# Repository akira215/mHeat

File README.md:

# mHeat
Monitoring HomeBus device and Modbus, embedded sofware on dedicated PCB using ESP32C6 µC

# Description

This repository contain all the development for an electronic device that will monitor a water tank (such as rain collect tank) using zigbee to transmit data to a coordinator. It contains: 
 * A PCB design [PCB design](PCB/README.md)
 * An enclosure design to be printed in 3D [Enclosure design](3Dprint/README.md)
 * Source code of the embedded software on the board (in an ESP32C6 µC)
 * An External converter for Zigbee2MQTT service [external converter](external_converters)

# Principle

The board will collect data from various sensors surch as:
 * Upstream static pressure (pump side)
 * Downstream static pressure (home side) - difference between upstream and downstream static pressure is used to estimate filters clogging
 * Water level sensor, to estimate the available water volume in the tank
 * water pulse meter to count the consumption in the home
 * Additionally on board temperature sensor could be monitor

 The 3 first sensors shall be 4-20mA sensor directly connected to the board. The water counter shall be a dry contact meter, connected to the board

 All these sensors have a calibration factor that can be updated directly form Zigbee2MQTT GUI. To avoid losing calibration, the device itself will keep updated theses factor in its Non Volatile Storage.

A 4-20mA input is available for any other futher sensor requirement. Adding a sensor will require to :
 * Update the embedded software
 * Update the external converter on Zigbee2MQTT side

## Usage

  * Short press button to join the zigbee network (coordinator shall grant pairing) -> LED shall flash, until network is joined, it then shutoff
  * Long press button to leave network. When the LED is fixed on, the device is not connected to the network neither is trying to join

## Sensor selection

### Upstream and downstream static pressure

  Regular pressure transmitter are not so expensive and efficient for that purpose. These 2 sensors shall have a measured range according to installation pressure. In regular network, pressure is limited to 3 bars, so selecting a sensor 0-5 bars seems a good choice. If the upper value is higher, the resolution of the measurement will be less as the ADC converter resolution is fixed.

  The shunt to convert current to tension for the ADC converter is 133R, and Imax for the sensor @max range will be 20mA so Umax for ADS1115 will be 2.66V (U=R*I). 5 bars = 500 kPa, so the calibration factor shall be 500 kPa / 2.66V = 187.97 kPa/V. Of course this factor shall be adjusted by measuring at the same location of one sensor the pressure, and correcting the reading of the sensor, but this short computation can help to start setting up calibration factor

### Water level

  Whatever technology of sensor could be used as soon as its output is 4-20mA current. Tests have been done using submerged differential pressure sensor, with the balance pipe to get the atmospheric pressure that run with the electrical cable, they worked properly. The range of this sensor shall be in accordance with the depth of the tank. The output value of Zigbee2MQTT will be a % of depth (meaning 100% when tank is full). Depending on the shape and cross section of the tank, this could be converted to a volume directly in the Z2M external converter, or outside Z2M in another software.

  The shunt to convert current to tension for the ADC converter is 133R, and Imax for the sensor @max range will be 20mA so Umax for ADS1115 will be 2.66V (U=R*I). For 100% the calibration factor shall be 100% / 2.66V = 37.594 %/V. 
  
  Of course this factor shall be adjusted when tank is full to read 100% in the Zigbee2MQTT output. For example, if yo have a 0-2m sensor and the require stroke of your tank (max height - min height before depriming pump) is 1.5m, it means that the 100% value of your tank will occur when sensor will read 1.5m (take care to install the sensor just before depriming pump). The voltage at the converter will be 1.5m/2m * 2.66V = 1.995V, so you will have to set the calibration factor considering 100% / 1.995V = 50.125%/V

### Water pulse counter

  The water meter shall send a pulse each XX L, whatever XX is. It is expected to have a dry contact that switch on and off each pulse. Hardware debouncer has been implemented for a particular counter, measuring bouncing using an oscilloscope. Computation of this RC filter has been provided here:
  [Spreadsheet](<PCB/2024-06-29 Comput.ods>)
    
  The kFactor to be set up in Zigbee2MQTT is only the L per pulse of the counter.

## Zigbee2MQTT integration

### External converter

External converter shall be loaded according to Zigbee2MQTT instructions:

[Zigbee2MQTT external converters](https://www.zigbee2mqtt.io/advanced/more/external_converters.html)

Restart Zigbee2MQTT `Webpage > Settings > Tools > Restart Zigbee2MQTT`

### Pairing zTank device

If the LED is fixed on, short press one time on the button, this will put the device in pairing mode.
Device is in Pairing Mode when the LED flahes quickly. 

Put Coordinator (or other device) in pairing mode using Zigbee2MQTT GUI (antenna symbol on the upper right of the screen with mention `All`)

After a short time, LED shall stop flashing. When LED is off, device is paired. You can check on Zigbee2MQTT device list

### Device icon

To add an icon in Zigbee2MQTT GUI, create a folder named `device_icon` in the root of Zigbee2MQTT docker installation (folder containing `configuration.yml`). In that foler, put the `zTank_icon.png` file contained in the `img` directory of this repository.

On Zigbee2MQTT GUI, go to `Devices` list and click on the device. Go to `Settings` tab and scroll down to the `icon` box.
Put `device_icons/zTank_icon.png` in that box. Icon shall be visible on Zigbee2MQTT GUI.

### Reporting

To develop*******************************************************************

## Build Instructions

The embedded software required `esp-ash-components`:

```
git submodule add https://github.com/akira215/esp-ash-components.git components
```

Create a partition.csv for zigbee and configure menuconfig with custom partition table (shall be done by default)

## Configuration

Configuration is available in `menuconfig` in the `Project setting` section:

### Pin Layout

  This section refer to hardware connection of LED button and volume meter. <span style="color:red">**These settings shall not be changed unless new hardware is developped.**</span>

### Zigbee endpoints

  This section refer to the endpoint for each sensor of the device. Any change in this number require to update the external converter accordingly

  And in Zigbee2MQTT external converter:

### Zigbee device

  Zigbee stack has been sized doing extensive tests. <span style="color:red">**This setting shall not be changed.**</span>

### ADS Pin Layout

  This section refer to hardware connection of ADS1115 converter to µC pin. <span style="color:red">**These settings shall not be changed unless new hardware is developped.**</span>

### ADS Converter config

  The first 3 inputs refer to the channel in which each sensor is connected. Take care that channel are not implemented on the connector in a logical order, so please refer to pictures that describe which pins of the connector is connected to which ADC channel (and polarity for sensors)

  The delay between 2 queries of ADS is the update rate of the measurement. Between 2 measurement, ADS is put in sleep to optimize consumption. Take care that driver will trigger one conversion for each channel, so there is a minimal time between 2 queries, depending on the resolution set for the ADS.

  The delay between 2 queries of temperature is the update rate of the measurement of the internal µC temperature sensor.

## Current Status

Still work in progress, but is completely running. All bugs 
could be reported to try to improve it.

## PCB design

[PCB design](PCB/README.md)

## Enclosure design design

[Enclosure design](3Dprint/README.md)

## Caveats

### To be developped

OTA update

## Usage and Examples

## Changes

### New in version 0.0.0

## Credits

 * [Zigbee2MQTT](https://github.com/Koenkk/zigbee2mqtt)

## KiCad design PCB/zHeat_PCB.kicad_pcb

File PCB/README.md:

# zHeat PCB
A dedicated PCB using ESP32C6 µC as been designed to optimize reliability and costs.

The board connect to:

* Homebus to connect Daikin Heat Pump via P1P2 connector

* 12V serial bus to connect on heating circuit controller

* 4-20mA port to connect to pressure sensor on the circuit

## Tools

 The design of the PCB has been done with KiCad 10.0. Particular footprint and 3D STEP file are included in the `/library` folder for sake of maintenance

## Design

 The design is based on ESP32C6 WROOM with the following peripherials:
 * USB for power, flash device and output serial debug / info.
 * Powering circuit is done using MCP1826S 
 * A 4-20mA loop is built based on a LM2735X (1.6MHz) to raise voltage to about 20V
 * 4 channels 4-20mA sensors is provided and converted using ADS1115IDGS. It communicate with µC with i2c port
 * a debounced contact is provided for pulse counter
 * A push button is also provided for very simple HMI
 * PCB is also equipped by a LED for simpl HMI
 * Finally PCB is equipped with header that can be used for a touchscreen device in case of future needs (software lib already written and tested)

 Component size has been selected to 0805, except ESD protective diodes that are smaller.

### USB

  USB socket is grounded to the main ground planes (2 sides).
  USB Lines `USB-` and `USB+` are directly connected to ESP32C6 to flash and monitor µC.
  `VBUS` is used to provide `+5V` (which is in fact lower than +5V) via a protective diode `D3`.

  All this 3 lines are protected by ESD protective diode.

### Voltage regulator

  All the board is powered using `+3.3V`. This voltage is provided by a fixed low-voltage regulator MCP1826S-3302E that can provide up to 1000mA.
  Fixed voltage regulator requires only few external component, in this case only capacitors are installed as per datasheet.

### 4-20mA Voltage circuit

  To avoid noise on lines and due to voltage drop at each stage, 4-20mA loop voltage shall be at around 20V. Care shall be taken when changing this voltage as it may require adjustment (in the shunt values for instance) to avoid damaging other components.

  This voltage is produced from `+5V` using a boost type regulator LM2735X (@1.6MHz). Computation of the external components are provided in the LibreOffice Spreadsheet [PCB comput spreadsheet](<2024-06-29 Comput.ods>). A 33µH inductance has been selected to get a clean output voltage to avoid noise on sensors line.

### 4-20mA conversion

  4 channels are available via Phoenix contact 8 poles connector. Each channel input current is injected in a 133R shunt (low tolerance resistor) to output a voltage below 3.3V. A 100nF capacitor is provided to reduce noise.

  Each channel voltage is then converted in a digital signal using an ADS1115IDGS, that communicate with µC using i2c protocol. A ready pin is used to trigger an interrupt to the µC when data are available.
  External components are:
   * 10k resistor connected to the ground for the address of the device (only one on board so gnd is the common one)
   * 10k pull-up resistor on each signal (`SCL`, `SDA`, `RDY`) connected to µC
   * Decoupling capacitor for power lines and rearmable fuse to protect circuit

### Debounced contact

An harware RC filter has been set up on this input to avoid false triggering. The computation of this filter is detailed in the spreadsheet file [PCB comput spreadsheet](<2024-06-29 Comput.ods>), bouncing duration has been measured using an oscilloscope in a unique water meter equiped with dry contact pulse output. It may be required to adjust this filter if the water meter seems to input false pulse to the µC. 

The only other component is a pull-up resistor to not let a float input.

### µC ESP32C6 WROOM

ESP32C6 power up is done using decoupling capacitor (10µF // 100nF).

The `EN` pin is driven to the `+3.3V` to enable the µC. 

`GPIO9` shall be pulled up to `+3.3V` to set the µC in normal execution mode (instead of ROM serial bootloader when `GPIO9` is pulled to the ground). Despite the doc says that it has an internal pull-up, µC will not boot normally after reporg if not driven to `+3.3V`.

`GPIO8` shall be driven to `+3.3V` as doc says, in order to enter the serial bootloader reliably.

### Push Button

Push button has been connected to `GPIO9`, so it can be used to boot/flash device by driving the pin low. Indeed, no operation is required on this button to flash µC using USB directly, and push button is used by software for HMI purpose.

### Led

A led is connected to `GPIO23` for HMI purpose as well. Resistor has been calculated according to LED spec to grant the required current.

### Header

A header is available to drive a touchscreen if required. It has not been integrated in the enclosure of this repo. It was planned and tested using a ILI9341 TFT touchscreen.

## PCB fabrication

Gerber files are included for fabrication. A batch of PCB has been produced by JLCPCB with the following configuration:

|Base Material        |	FR-4	                             | Layers                     |	2                 |
|---------------------|------------------------------------|----------------------------|-------------------|
|Dimension            |	49 mm* 91 mm                       | PCB Qty                    |	20                |
|Product Type         |	Industrial/Consumer electronics    | Different Design           |	1                 |
|Delivery Format      |	Single PCB	                       | PCB Thickness              |	1.6mm             |
|Specify Stackup      |	no	                               | Layer Sequence             |                   |	
|PCB Color            |	Purple	                           | Silkscreen                 |	White             |
|Material Type        |	TG135	                             | Via Covering               |	Tented            |
|Surface Finish       |	ENIG Gold Thickness: 1U"	         | Deburring/Edge rounding    |	No                |
|Outer Copper Weight  |	1 oz	                             | Gold Fingers               |	No                |
|Electrical Test      |	Flying Probe Fully Test	           | Castellated Holes          |	no                |
|Edge Plating         |	No	                               | Mark on PCB	              | Order Number      |
|Blind Slot           |	No	                               | Min via hole size/diameter |	0.3mm/(0.4/0.45mm)|
|4-Wire Kelvin Test   |	No	                               | Paper between PCBs         |	No                |
|Appearance Quality   |	IPC Class 2 Standard	             | Confirm Production file    |	No                |
|Silkscreen Technology|	Ink-jet/Screen Printing Silkscreen | Package Box                |	With JLCPCB logo  |
|Inspection Report    |	No	                               | Board Outline Tolerance    |	±0.2mm(Regular)   |
|UL Marking           |	No	                               | Countersink Hole           |	No                |

## Assembly

A stencil as been produced by JLCPCB, so the assembly has been done using solder paste, manually placing components, and reflow is done using an hot plate.

The components that generate issues during that process are:
 * USB connector `J5` : often some bridges are created due to the high density of pin. It has to be manually fixed
 * ESD protection diodes `D4`, `D5` & `D6`: are they are really small and light, they moved during the reflow process. It has to be manually fixed with a soldering iron, as hot air gun make them move anyway whaterver the airflow is
 * Care should be taken on the pin of ADS converter `U1`(bridges) and µC `U4` (alke of solder)
 * Obviously connector `J1`, `J2` and `J3` have to be solded manually

## Usage

For routing simplicity, 4-20mA channels are not reparted logically on the board, please consider the scheme here below.

Debounced pulse contact don't have polarity.

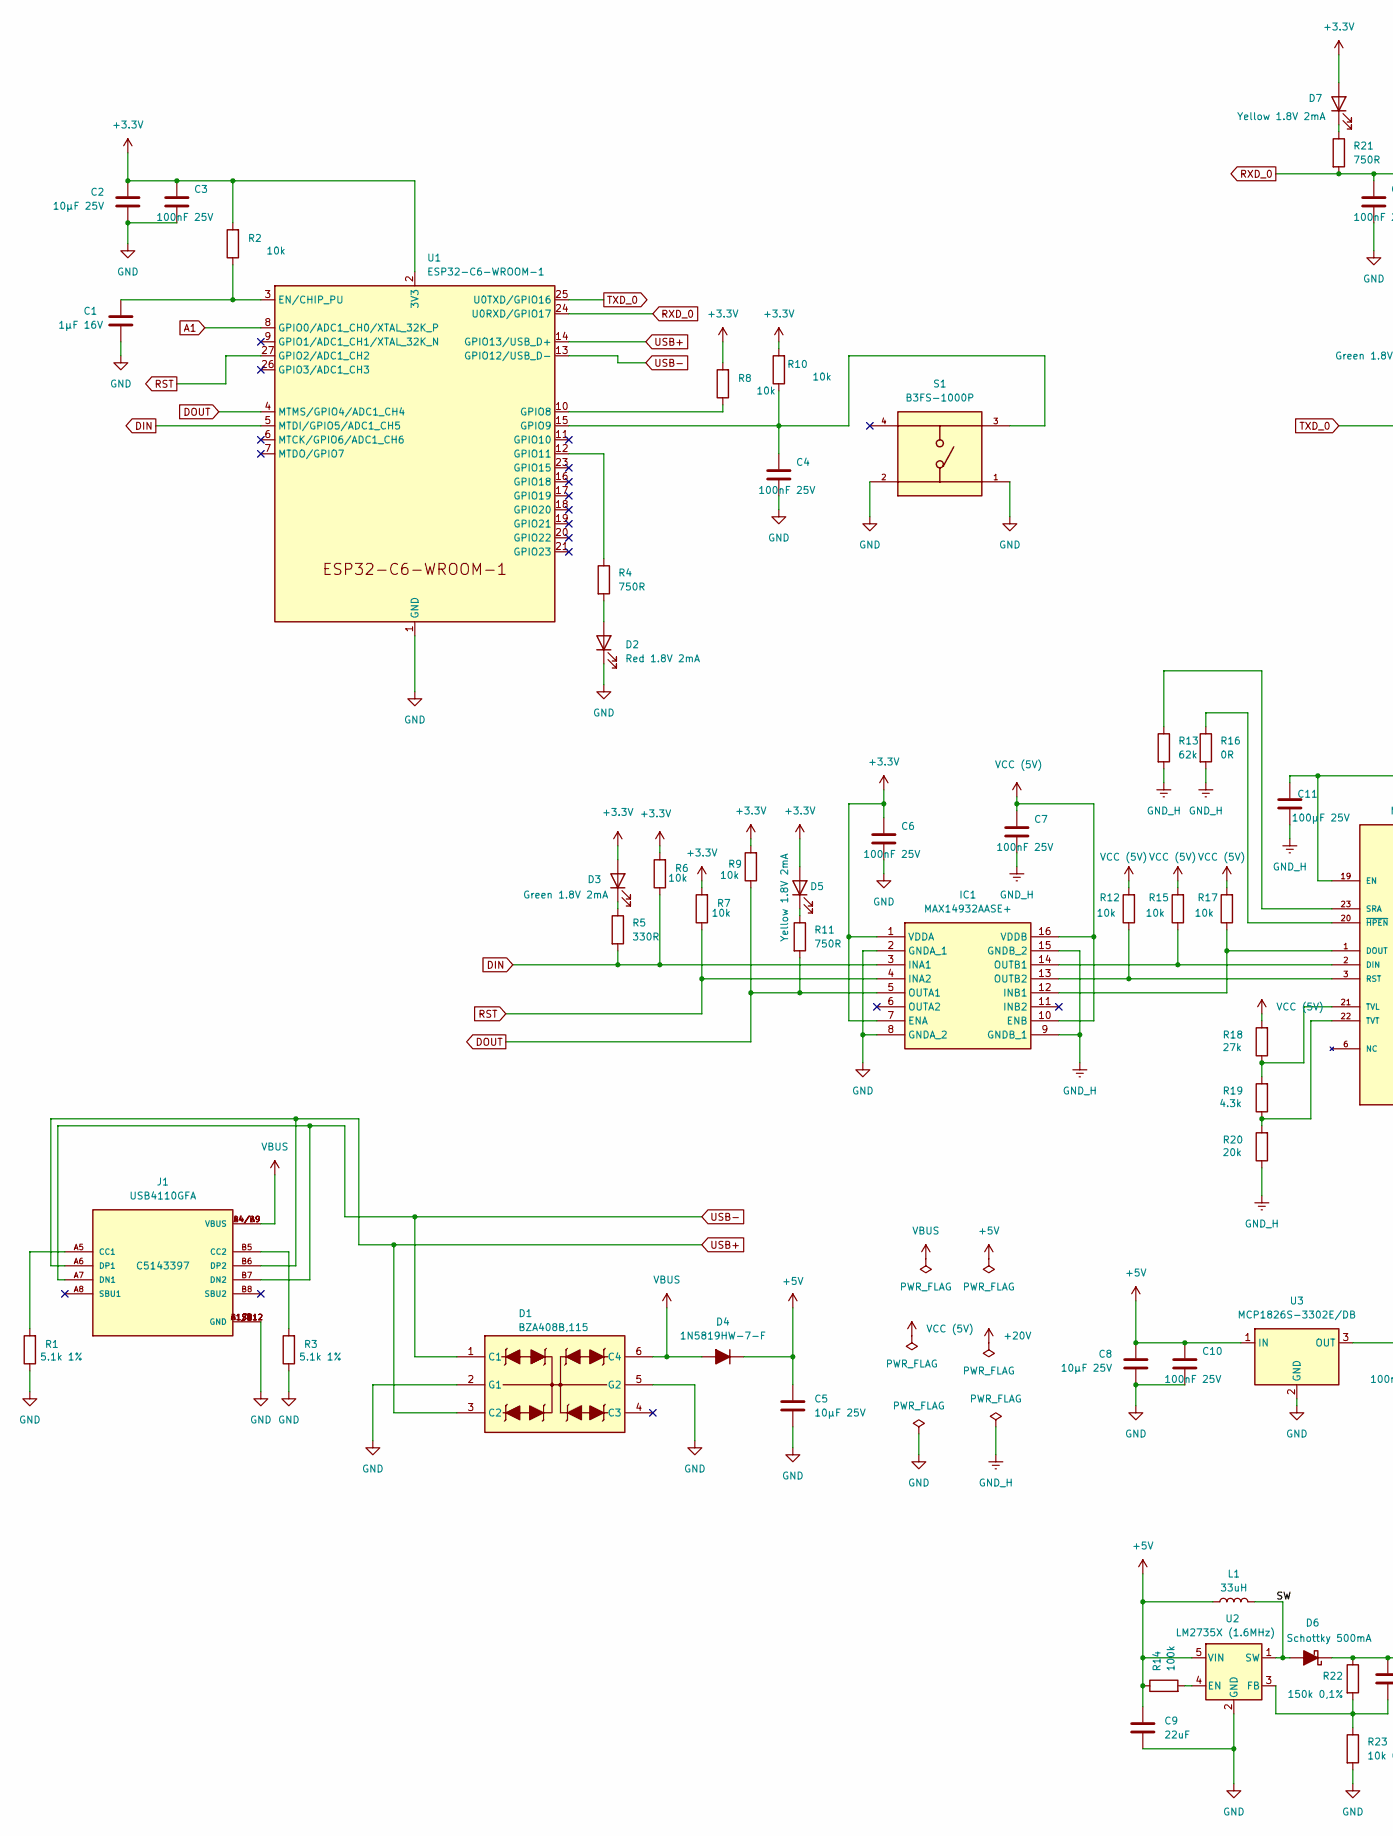
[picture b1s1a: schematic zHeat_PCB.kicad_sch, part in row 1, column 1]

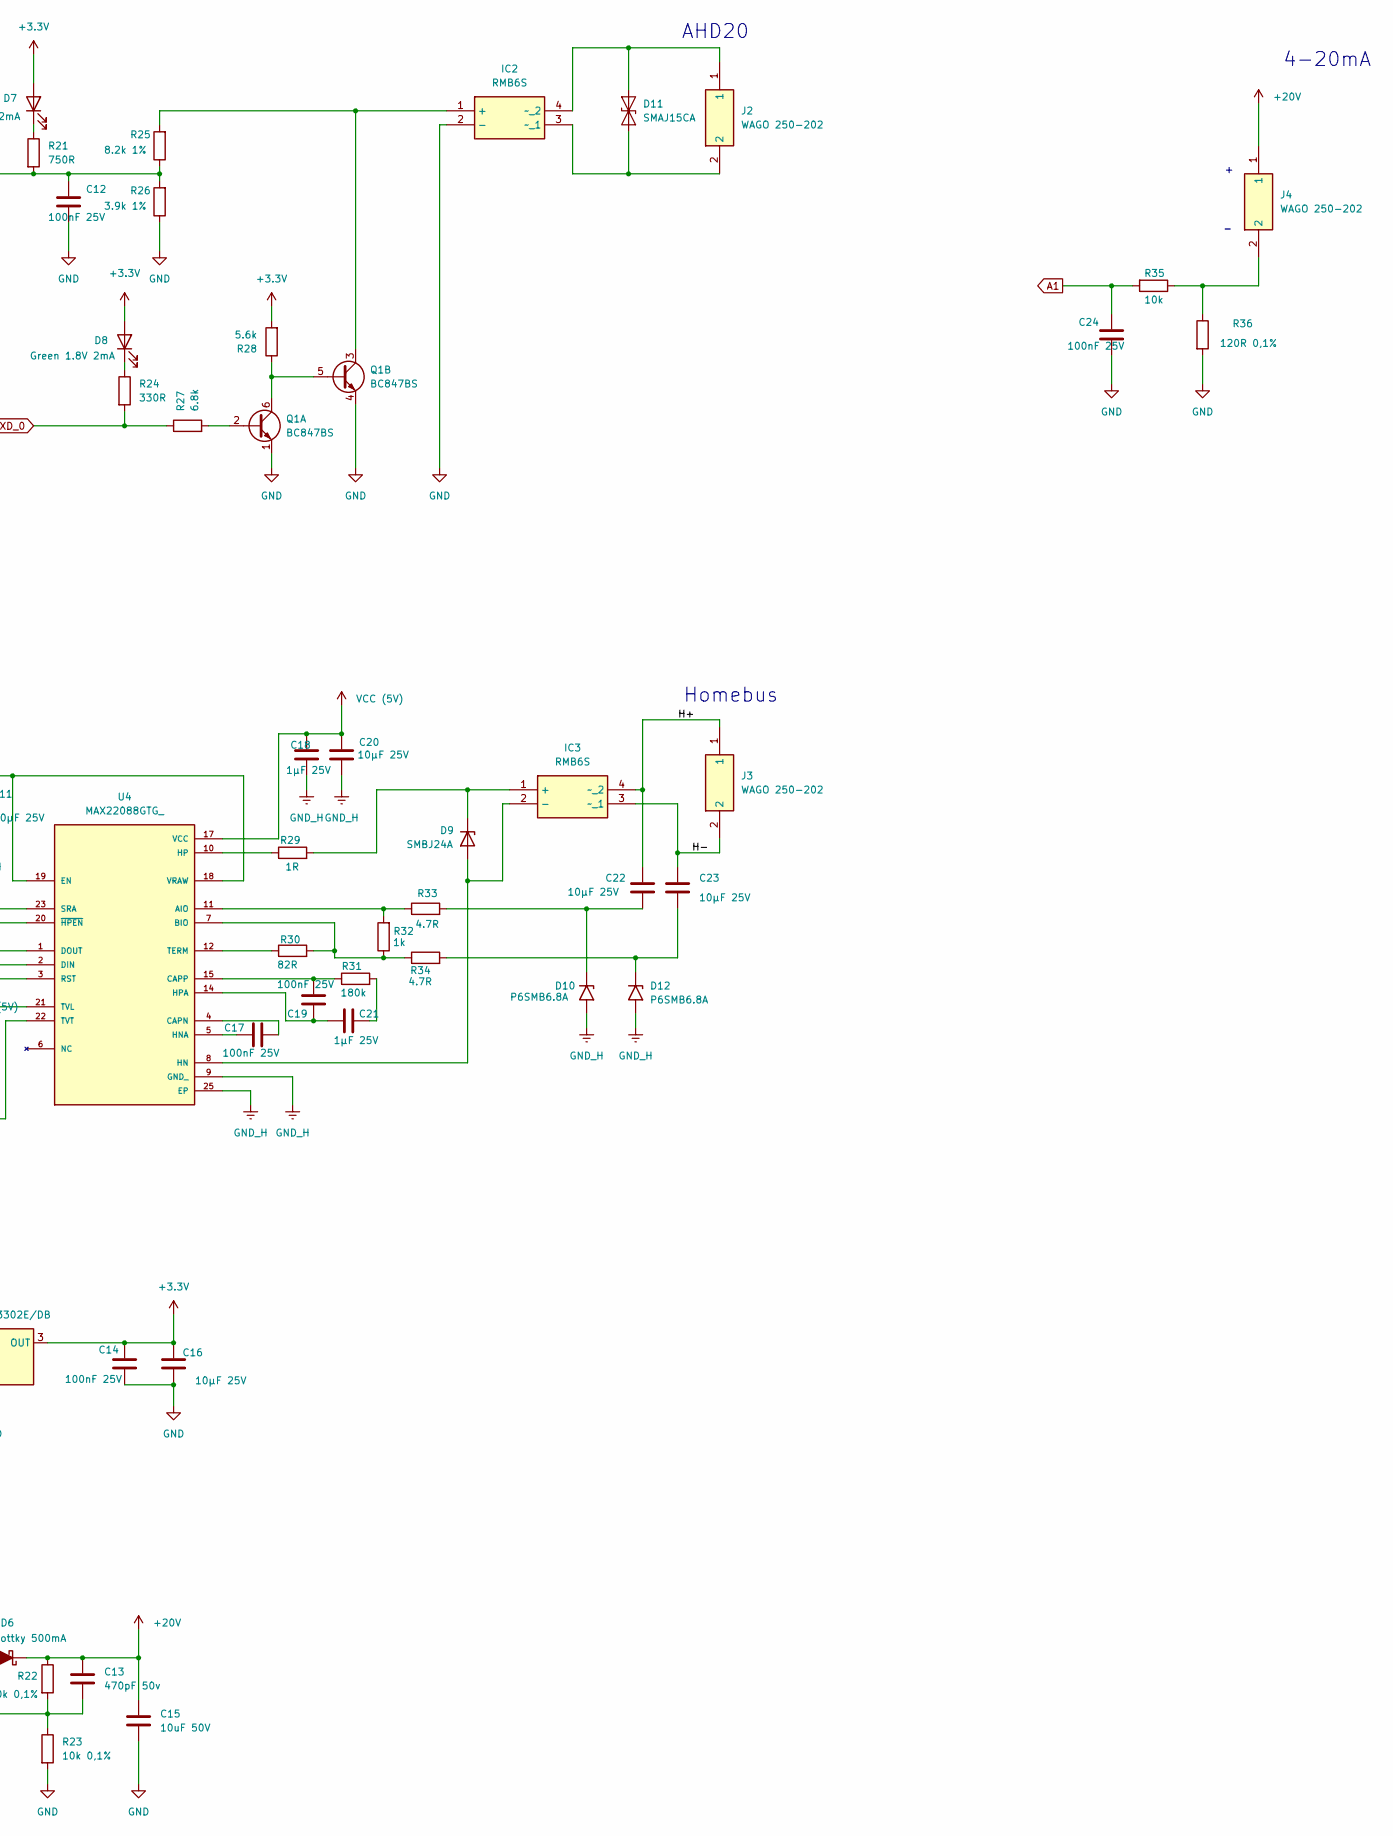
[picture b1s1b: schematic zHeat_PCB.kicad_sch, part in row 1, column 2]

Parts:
C1: 1µF 16V; C_0805_2012Metric; LCSC C94122
C2, C5, C8, C16, C20, C22, C23: 10µF 25V; C_0805_2012Metric; LCSC C669099
C3, C4, C6, C7, C10, C12, C14, C17, C19, C24: 100nF 25V; C_0805_2012Metric; LCSC C519981
C9: 22uF; C_0805_2012Metric; LCSC C45783
C11: 100µF 25V; CP_Elec_6.3x7.7; LCSC C2836443
C13: 470pF 50v; C_0805_2012Metric; LCSC C1743
C15: 10uF 50V; C_0805_2012Metric; LCSC C22367830
C18, C21: 1µF 25V; C_0805_2012Metric; LCSC C91186
D1: BZA408B,115; SOT95P275X110-6N; Mouser Part Number 771-BZA408B,125
D2: Red 1.8V 2mA; D_0805_2012Metric; LCSC C5879380
D3, D8: Green 1.8V 2mA; D_0805_2012Metric; LCSC C5569446
D4: 1N5819HW-7-F; D_SOD-123; LCSC C82544
D5, D7: Yellow 1.8V 2mA; D_0805_2012Metric; LCSC C5879382
D6: Schottky 500mA; D_SOD-123; LCSC C52747980
D9: SMBJ24A; D_SMB; LCSC C224017
D10, D12: P6SMB6.8A; D_SMB; LCSC C2758562
D11: SMAJ15CA; D_SMA; LCSC C110044
IC1: MAX14932AASE+; SOIC127P600X175-16N; Mouser Part Number 700-MAX14932AASE+
IC2, IC3: RMB6S; TO-269AA; Mouser Part Number 512-MB1S
J1: USB4110GFA; GCT_USB4110GFA; LCSC C5143397
J2, J3, J4: WAGO 250-202; CONN2_250-202_WAG; Mouser Part Number 651-1985195
L1: 33uH; CDRH104RNP330NC; LCSC C225051
Q1: BC847BS; SOT-363_SC-70-6; LCSC C8653
R1, R3: 5.1k 1%; R_0805_2012Metric; LCSC C27834
R2, R6, R7, R8, R9, R10, R12, R15, R17, R35: 10k; R_0805_2012Metric; LCSC C17414
R4, R11, R21: 750R; R_0805_2012Metric; LCSC C17818
R5, R24: 330R; R_0805_2012Metric; LCSC C17630
R13: 62k; R_0805_2012Metric; LCSC C17783
R14: 100k; R_0805_2012Metric; LCSC C100049
R16: 0R; R_0805_2012Metric; LCSC C174076
R18: 27k; R_0805_2012Metric; LCSC C114533
R19: 4.3k; R_0805_2012Metric; LCSC C137518
R20: 20k; R_0805_2012Metric; LCSC C4328
R22: 150k 0,1%; R_0805_2012Metric; LCSC C136927
R23: 10k 0,1%; R_0805_2012Metric; LCSC C110775
R25: 8.2k 1%; R_0805_2012Metric; LCSC C17828
R26: 3.9k 1%; R_0805_2012Metric; LCSC C114221
R27: 6.8k; R_0805_2012Metric; LCSC C114550
R28: 5.6k; R_0805_2012Metric; LCSC C114538
R29: 1R; R_0805_2012Metric; LCSC C25271
R30: 82R; R_0805_2012Metric; LCSC C17841
R31: 180k; R_0805_2012Metric; LCSC C17501
R32: 1k; R_0805_2012Metric; LCSC C17513
R33, R34: 4.7R; R_0805_2012Metric; LCSC C17675
R36: 120R 0,1%; R_0805_2012Metric; LCSC C2989047
S1: B3FS-1000P; PARTREV 1.0; LCSC C271750
U1: ESP32-C6-WROOM-1; LCSC C5366877
U2: LM2735X (1.6MHz); SOT-23-5; LCSC C555454
U3: MCP1826S-3302E/DB; SOT-223-3_TabPin2; LCSC C638624
U4: MAX22088GTG_; QFN50P400X400X80-25N; PARTREV 4; LCSC C5258925

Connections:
+3.3V: C2.1, C3.1, C6.1, C14.1, C16.1, D3.2 (A), D5.2 (A), D7.2 (A), D8.2 (A), IC1.1 (VDDA), IC1.7 (ENA), R2.2, R6.2, R7.2, R8.2, R9.2, R10.2, R28.2, U1.2 (3V3), U3.3 (OUT)
+5V: C5.1, C8.1, C9.1, C10.1, D4.1 (K), L1.1, R14.1, U2.5 (VIN), U3.1 (IN)
+20V: C13.1, C15.1, D6.1 (K), J4.1, R22.1
/H+: C22.1, IC3.4 (~_2), J3.1
/H-: C23.1, IC3.3 (~_1), J3.2
/SW: D6.2 (A), L1.2, U2.1 (SW)
A1: C24.1, R35.2, U1.8 (GPIO0/ADC1_CH0/XTAL_32K_P)
DIN: IC1.3 (INA1), R5.2, R6.1, U1.5 (MTDI/GPIO5/ADC1_CH5)
DOUT: IC1.5 (OUTA1), R9.1, R11.2, U1.4 (MTMS/GPIO4/ADC1_CH4)
GND: C1.2, C2.2, C3.2, C4.2, C5.2, C6.2, C8.2, C9.2, C10.2, C12.2, C14.2, C15.2, C16.2, C24.2, D1.2 (G1), D1.5 (G2), D2.1 (K), IC1.2 (GNDA_1), IC1.8 (GNDA_2), IC2.2 (-), J1.A1/B12 (GND), J1.B1/A12 (GND), J1.S1 (GND), J1.S2 (GND), J1.S3 (GND), J1.S4 (GND), Q1.1 (E1), Q1.4 (E2), R1.1, R3.1, R23.2, R26.1, R36.2, S1.1, S1.2, U1.1 (GND), U1.28 (GND), U1.29 (GND), U2.2 (GND), U3.2 (GND)
GND_H: C7.2, C11.2, C18.2, C20.2, D10.2 (A2), D12.2 (A2), IC1.9 (GNDB_1), IC1.15 (GNDB_2), R13.2, R16.2, R20.1, U4.9 (GND_), U4.16 (GND_), U4.25 (EP)
unnamed: C21.1, R31.2
unnamed: D2.2 (A), R4.2
unnamed: D3.1 (K), R5.1
unnamed: D5.1 (K), R11.1
unnamed: D7.1 (K), R21.1
unnamed: D8.1 (K), R24.1
unnamed: D9.2 (A), IC3.2 (-), U4.8 (HN)
unnamed: D9.1 (K), IC3.1 (+), R29.2
unnamed: C22.2, D10.1 (A1), R33.2
unnamed: D11.1 (A1), IC2.3 (~_1), J2.2
unnamed: D11.2 (A2), IC2.4 (~_2), J2.1
unnamed: C23.2, D12.1 (A1), R34.2
unnamed: IC1.12 (INB1), R17.1, U4.1 (DOUT)
unnamed: IC1.14 (OUTB1), R15.1, U4.2 (DIN)
unnamed: IC1.13 (OUTB2), R12.1, U4.3 (RST)
unnamed: IC2.1 (+), Q1.3 (C2), R25.2
unnamed: J1.A5 (CC1), R1.2
unnamed: J1.B5 (CC2), R3.2
unnamed: J4.2, R35.1, R36.1
unnamed: Q1.2 (B1), R27.2
unnamed: Q1.5 (B2), Q1.6 (C1), R28.1
unnamed: C1.1, R2.1, U1.3 (EN/CHIP_PU)
unnamed: R8.1, U1.10 (GPIO8)
unnamed: C4.1, R10.1, S1.3, U1.15 (GPIO9)
unnamed: R4.1, U1.12 (GPIO11)
unnamed: R14.2, U2.4 (EN)
unnamed: C13.2, R22.2, R23.1, U2.3 (FB)
unnamed: R32.2, R33.1, U4.11 (AIO)
unnamed: R30.2, R32.1, R34.1, U4.7 (BIO)
unnamed: C17.2, U4.4 (CAPN)
unnamed: C19.2, R31.1, U4.15 (CAPP)
unnamed: C11.1, U4.18 (VRAW), U4.19 (EN)
unnamed: C17.1, U4.5 (HNA)
unnamed: R29.1, U4.10 (HP)
unnamed: C19.1, C21.2, U4.14 (HPA)
unnamed: R13.1, U4.23 (SRA)
unnamed: R30.1, U4.12 (TERM)
unnamed: R18.1, R19.2, U4.21 (TVL)
unnamed: R19.1, R20.2, U4.22 (TVT)
unnamed: R16.1, U4.20 (~HPEN)
RST: IC1.4 (INA2), R7.1, U1.27 (GPIO2/ADC1_CH2)
RXD_0: C12.1, R21.2, R25.1, R26.2, U1.24 (U0RXD/GPIO17)
TXD_0: R24.2, R27.1, U1.25 (U0TXD/GPIO16)
USB+: D1.3 (C2), J1.A6 (DP1), J1.B6 (DP2), U1.14 (GPIO13/USB_D+)
USB-: D1.1 (C1), J1.A7 (DN1), J1.B7 (DN2), U1.13 (GPIO12/USB_D-)
VBUS: D1.6 (C4), D4.2 (A), J1.A4/B9 (VBUS), J1.B4/A9 (VBUS)
VCC (5V): C7.1, C18.1, C20.1, IC1.10 (ENB), IC1.16 (VDDB), R12.2, R15.2, R17.2, R18.2, U4.17 (VCC)

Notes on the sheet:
AHD20
Homebus
4-20mA

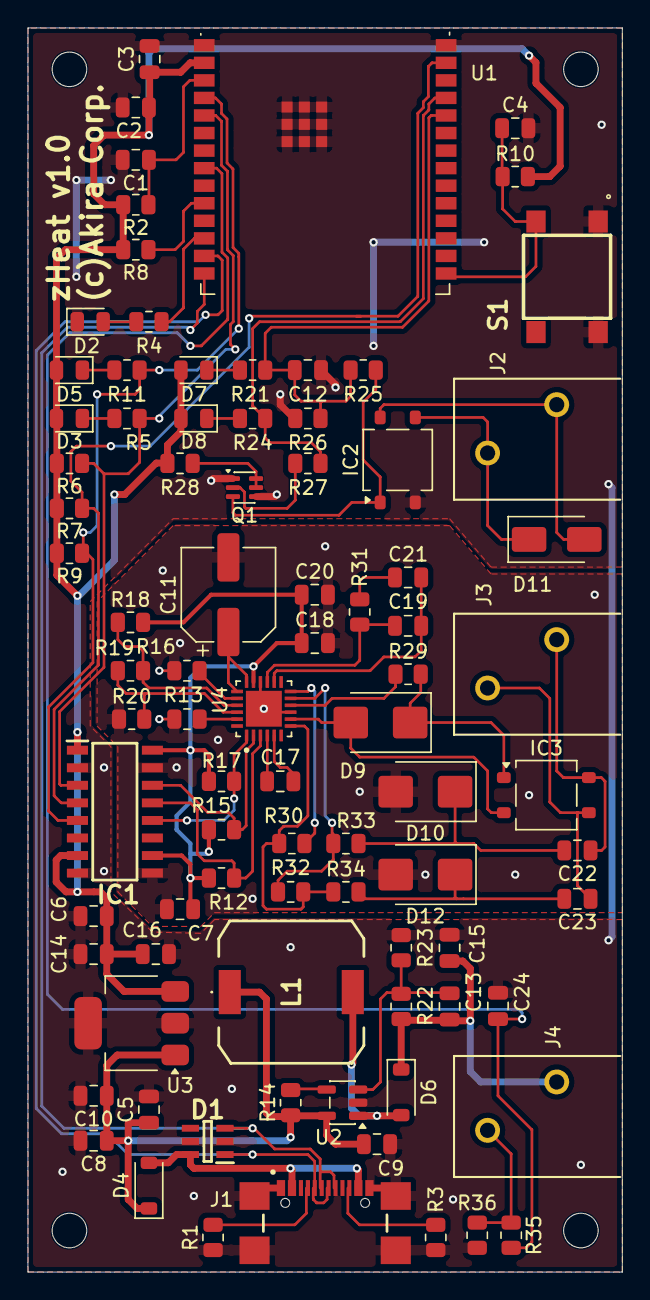
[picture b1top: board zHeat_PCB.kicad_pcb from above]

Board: 2 copper layers, 43.0 x 90.0 mm, 86 parts (0 on the bottom side), 58 nets.

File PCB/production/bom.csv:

Designator,Footprint,Quantity,Value,LCSC Part #
C1,0805,1,1µF 16V,C94122
"C10, C12, C14, C17, C19, C24, C3, C4, C6, C7",0805,10,100nF 25V,C519981
C11,CP_Elec_6.3x7.7,1,100µF 25V,C2836443
C13,0805,1,470pF 50v,C1743
C15,0805,1,10uF 50V,C22367830
"C16, C2, C20, C22, C23, C5, C8",0805,7,10µF 25V,C669099
"C18, C21",0805,2,1µF 25V,C91186
C9,0805,1,22uF,C45783
D1,SOT95P275X110-6N,1,"BZA408B,115",C550053
"D10, D12",D_SMB,2,P6SMB6.8A,C2758562
D11,D_SMA,1,SMAJ15CA,C110044
D2,0805,1,Red 1.8V 2mA,C5879380
"D3, D8",0805,2,Green 1.8V 2mA,C5569446
D4,D_SOD-123,1,1N5819HW-7-F,C82544
"D5, D7",0805,2,Yellow 1.8V 2mA,C5879382
D6,D_SOD-123,1,Schottky 500mA,C52747980
D9,D_SMB,1,SMBJ24A,C224017
IC1,SOIC127P600X175-16N,1,MAX14932AASE+,C7451518
"IC2, IC3",TO-269AA,2,RMB6S,C3589251
J1,GCT_USB4110GFA,1,USB4110GFA,C5143397
"J2, J3, J4",CONN2_250-202_WAG,3,WAGO 250-202,C2765061
L1,CDRH104RNP330NC,1,33uH,C225051
Q1,SOT-363_SC-70-6,1,BC847BS,C8653
"R1, R3",0805,2,5.1k 1%,C27834
"R10, R12, R15, R17, R2, R35, R6, R7, R8, R9",0805,10,10k,C17414
"R11, R21, R4",0805,3,750R,C17818
R13,0805,1,62k,C17783
R14,0805,1,100k,C100049
R16,0805,1,0R,C174076
R18,0805,1,27k,C114533
R19,0805,1,4.3k,C137518
R20,0805,1,20k,C4328
R22,0805,1,"150k 0,1%",C136927
R23,0805,1,"10k 0,1%",C110775
"R24, R5",0805,2,330R,C17630
R25,0805,1,8.2k 1%,C17828
R26,0805,1,3.9k 1%,C114221
R27,0805,1,6.8k,C114550
R28,0805,1,5.6k,C114538
R29,0805,1,1R,C25271
R30,0805,1,82R,C17841
R31,0805,1,180k,C17501
R32,0805,1,1k,C17513
"R33, R34",0805,2,4.7R,C17675
R36,0805,1,"120R 0,1%",C2989047
S1,B3FS-1000P,1,B3FS-1000P,C271750
U1,ESP32-C6-WROOM-1,1,ESP32-C6-WROOM-1,C5366877
U2,SOT-23-5,1,LM2735X (1.6MHz),C555454
U3,SOT-223-3_TabPin2,1,MCP1826S-3302E/DB,C638624
U4,QFN50P400X400X80-25N,1,MAX22088GTG_,C5258925

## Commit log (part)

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2026-06-02 project creation
2026-06-15 PCB for fabrication
